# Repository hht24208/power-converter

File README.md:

# STM32 Kontrollü SEPIC Güç Dönüştürücü (Öğrenci Projesi)

Bu repo, güç elektroniği ve kontrol teorisi konseptlerini birleştirerek pratik bir donanıma dönüştürmeyi amaçlayan kişisel bir mühendislik projesidir. Temel hedef, geniş giriş voltajı aralıklarında çalışabilen, yazılım tabanlı (STM32) PID kontrolüne sahip bir SEPIC dönüştürücünün önce LTspice üzerinde matematiksel sınırlarını görmek, ardından gerçek donanımını inşa etmektir.

## 1. Güç Katı ve Donanım Mimarisi
Aşağıdaki şema, SEPIC topolojisinin güç katını ve temel geri besleme (feedback) yapısını göstermektedir. Sistemi mikrodenetleyici ile güvenli bir şekilde sürebilmek için **TC4427** gate sürücü entegresi kullanıldı. Akım ve gerilim okumaları ise **LM358** op-ampları ile STM32'nin ADC pinlerine uygun seviyelere çekildi.

## 2. Matematiksel Modelleme ve Kontrolcü Tasarımı
SEPIC dönüştürücüler 4. dereceden non-lineer sistemler olduğu ve sağ yarı düzlem sıfırı (RHPZ) barındırdığı için, sadece deneme-yanılma ile kontrol edilmeleri oldukça zordur. Bu projede işin teorik kısmına inilerek, sistemin transfer fonksiyonuna uygun bir **Type-II/III Kompansatör** mantığı araştırılmış ve LTspice üzerinde s-domain (Laplace) denklemleriyle modellenmiştir.

## 3. Geçici Hal Yanıtı (Transient Response)
Aşağıdaki simülasyon çıktısında, sisteme aniden 12V giriş (Step Input) uygulandığında donanımın verdiği fiziksel tepki ve PID kontrolcünün davranışı incelenmiştir.
* Simülasyonun ilk milisaniyelerinde, SEPIC topolojisindeki uçan kondansatörün (flying capacitor) dolması sırasında oluşan doğal **Inrush Current (Başlangıç Şoku)** nedeniyle voltaj anlık olarak yükseliyor.
* Kontrolcü bu durumu yakalayarak PWM'i (Duty Cycle) %0'a çekiyor.
* Sistem yaklaşık 11. milisaniyede hedeflediğimiz **5V** seviyesine başarıyla oturarak regülasyonu sağlıyor.

---
*Not: Bu simülasyon aşaması, işin "yazılım-donanım takasını" (hardware vs. software trade-off) analiz etmek için yapılmıştır. İlerleyen aşamalarda KiCad ile PCB tasarımı yapılacak ve gerçek dünyadaki komponent toleransları STM32 üzerindeki C tabanlı bir kontrol algoritmasıyla yönetilmeye çalışılacaktır.*

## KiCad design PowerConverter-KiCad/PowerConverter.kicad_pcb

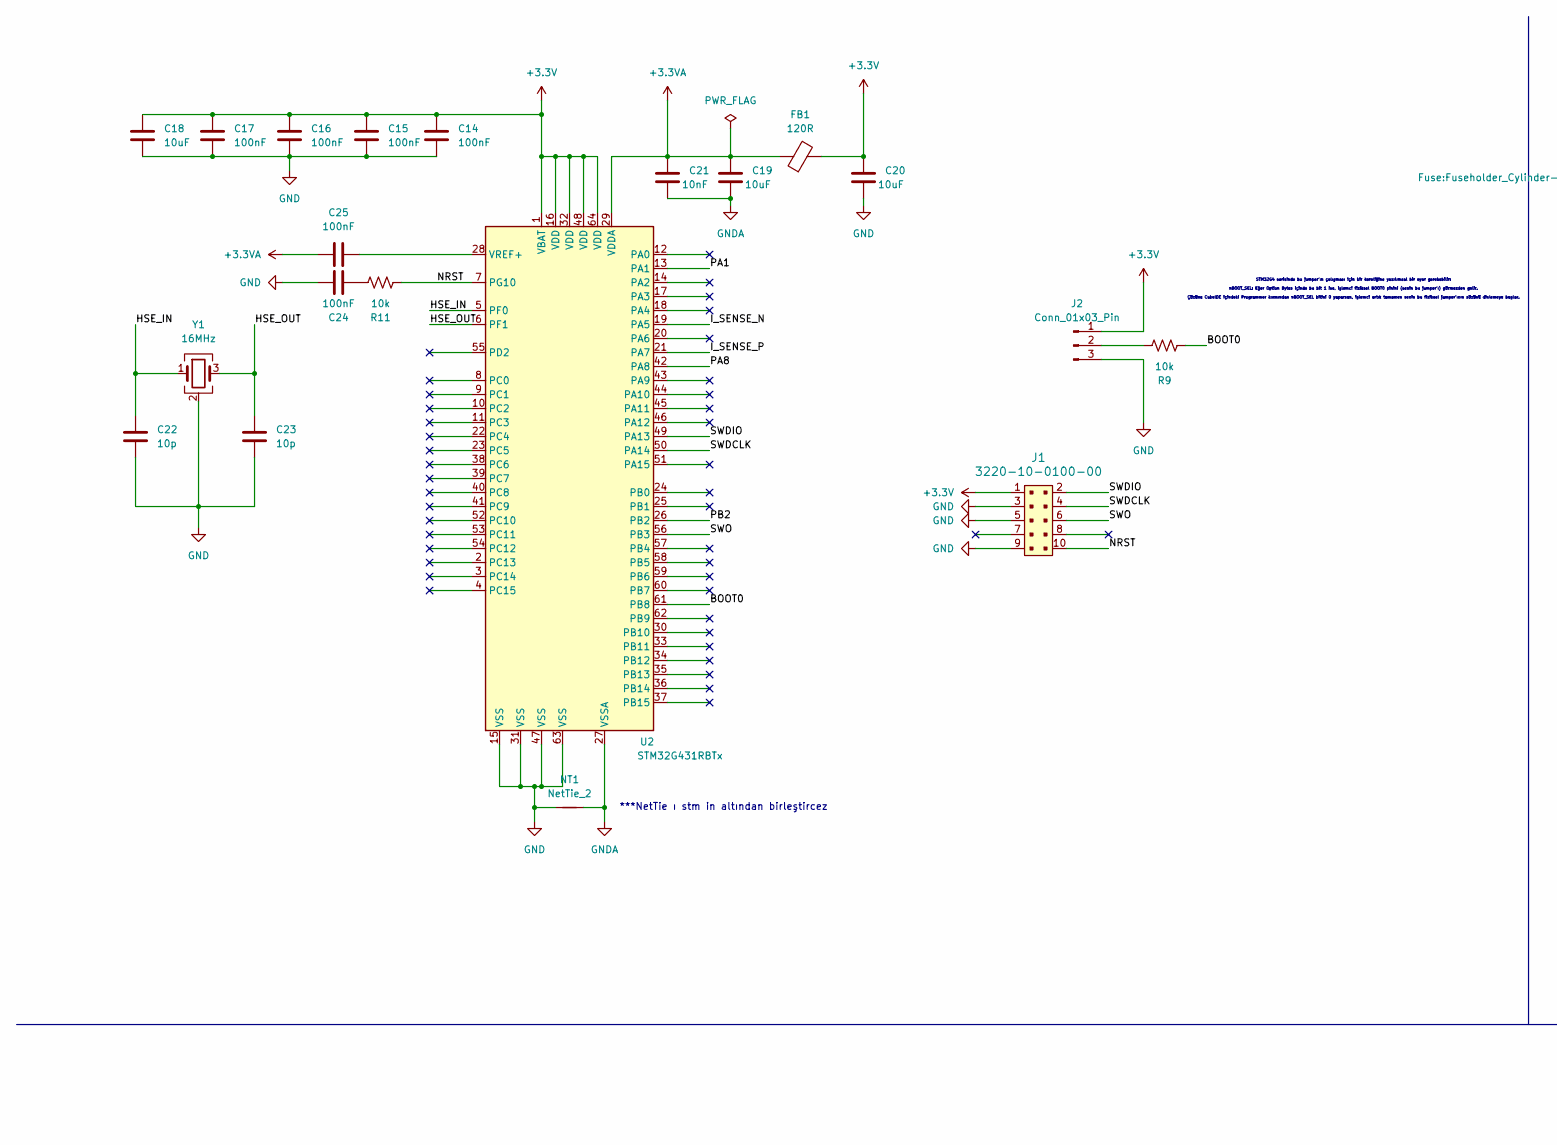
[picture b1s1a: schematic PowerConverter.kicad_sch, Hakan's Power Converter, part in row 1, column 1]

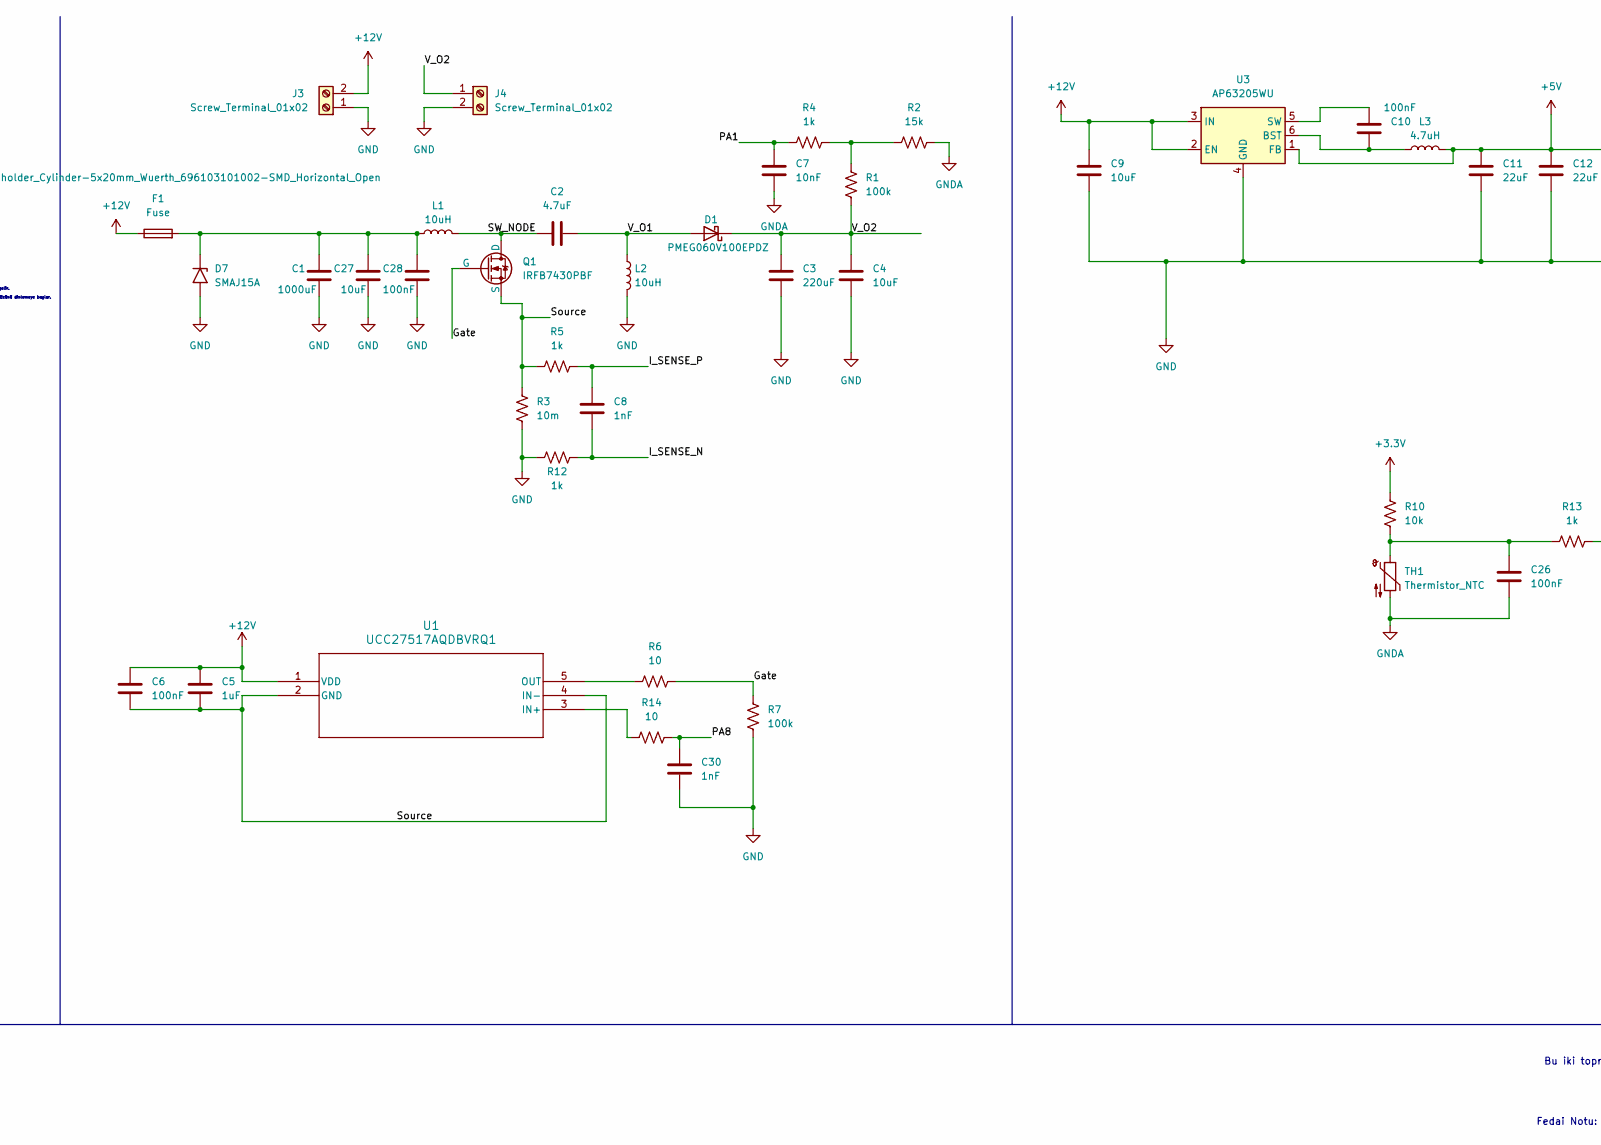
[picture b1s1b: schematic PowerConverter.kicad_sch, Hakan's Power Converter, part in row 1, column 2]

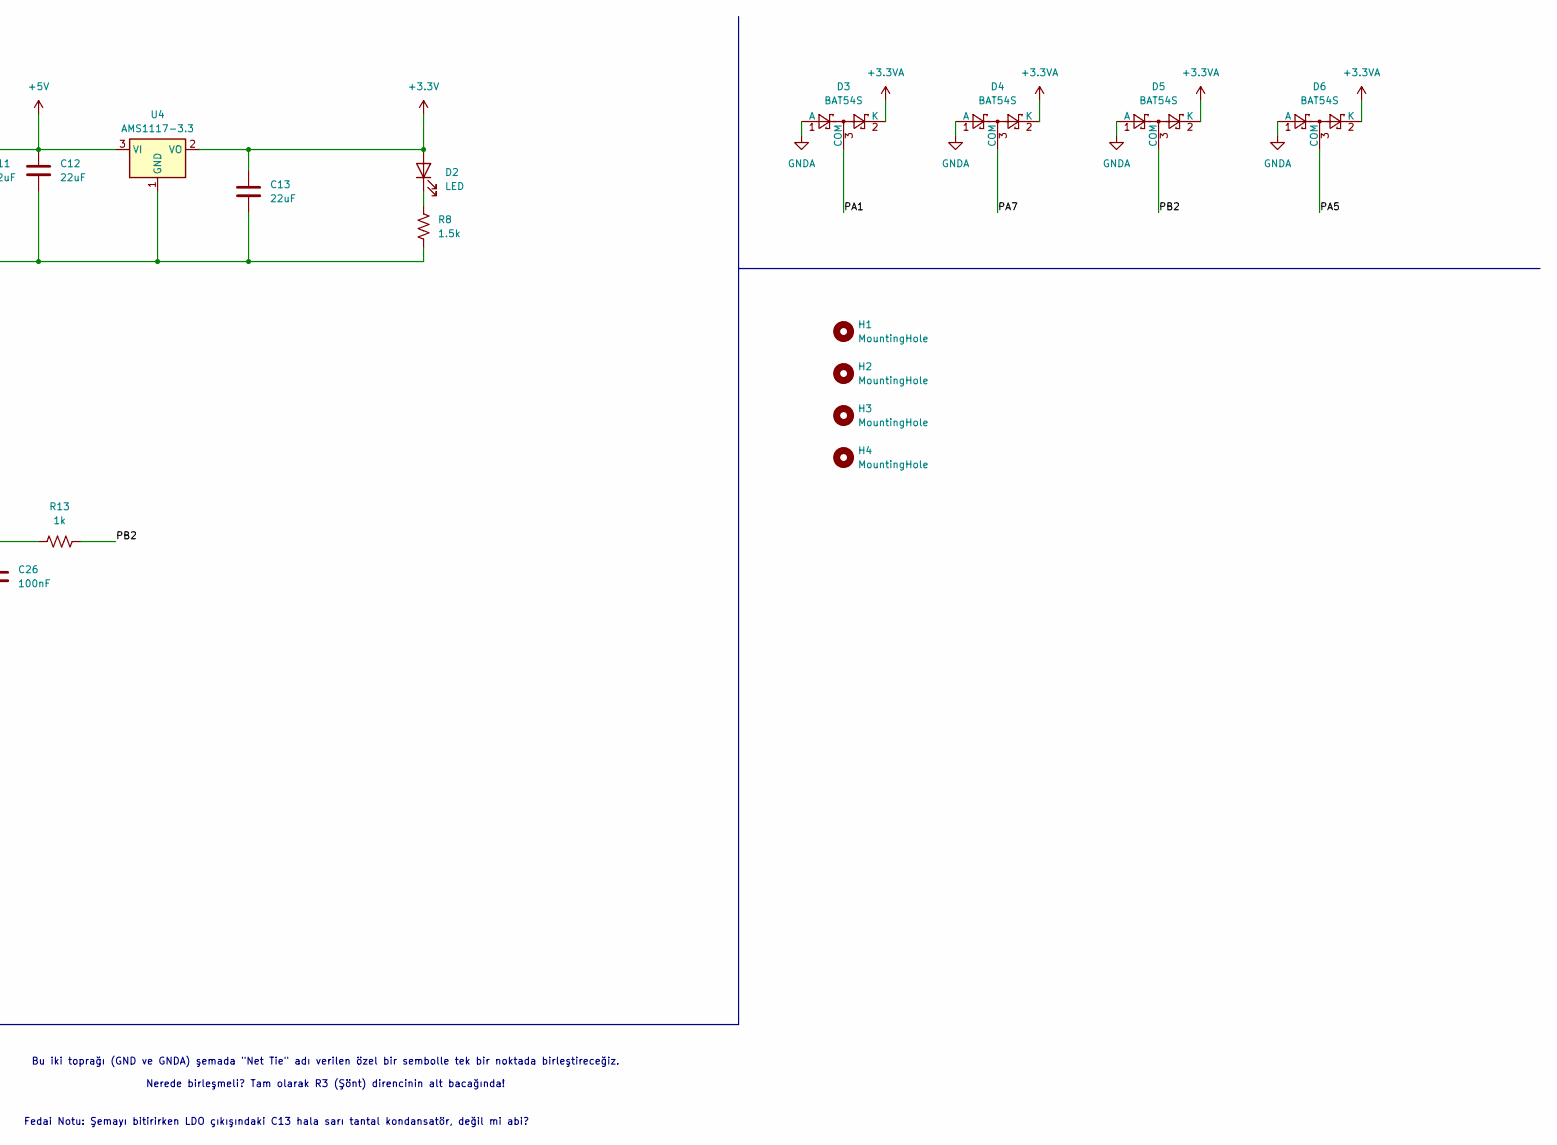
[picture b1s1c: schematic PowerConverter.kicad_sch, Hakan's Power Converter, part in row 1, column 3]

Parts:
C1: 1000uF; CP_Radial_D16.0mm_P7.50mm
C2: 4.7uF; C_1210_3225Metric_Pad1.33x2.70mm_HandSolder
C3: 220uF; CP_Radial_D8.0mm_P5.00mm
C4, C18, C19, C20, C27: 10uF; C_0805_2012Metric_Pad1.18x1.45mm_HandSolder
C5: 1uF; C_0805_2012Metric_Pad1.18x1.45mm_HandSolder
C6, C10, C14, C15, C16, C17, C24, C25, C26, C28: 100nF; C_0603_1608Metric_Pad1.08x0.95mm_HandSolder
C7, C21: 10nF; C_0603_1608Metric_Pad1.08x0.95mm_HandSolder
C8, C30: 1nF; C_0603_1608Metric_Pad1.08x0.95mm_HandSolder
C9: 10uF; C_1210_3225Metric_Pad1.33x2.70mm_HandSolder
C11, C12: 22uF; C_1210_3225Metric_Pad1.33x2.70mm_HandSolder
C13: 22uF; CP_EIA-3528-21_Kemet-B_HandSolder
C22, C23: 10p; C_0603_1608Metric_Pad1.08x0.95mm_HandSolder
D1: PMEG060V100EPDZ; TO-277B
D2: LED; LED_0805_2012Metric_Pad1.15x1.40mm_HandSolder
D3, D4, D5, D6: BAT54S; SOT-23
D7: SMAJ15A; D_SMC
F1: Fuse; Fuseholder_Cylinder-5x20mm_Wuerth_696103101002-SMD_Horizont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
FB1: 120R; L_0603_1608Metric
H1, H2, H3, H4: MountingHole; MountingHole_3.2mm_M3
J1: 3220-10-0100-00; PinHeader_2x5_P1.27mm_Drill.7mm; MPN 3220-10-0100-00; Digi-Key_PN 1175-1627-ND
J2: Conn_01x03_Pin; PinHeader_1x03_P2.54mm_Vertical
J3, J4: Screw_Terminal_01x02; Term_Block_1x2_P5.08MM
L1, L2: 10uH; L_Bourns_SRP1245A
L3: 4.7uH; L_Taiyo-Yuden_NR-30xx
NT1: NetTie_2; NetTie-2_SMD_Pad0.5mm
Q1: IRFB7430PBF; TO-220-3_Vertical
R1, R7: 100k; R_0603_1608Metric_Pad0.98x0.95mm_HandSolder
R2: 15k; R_0603_1608Metric_Pad0.98x0.95mm_HandSolder
R3: 10m; R_2512_6332Metric_Pad1.40x3.35mm_HandSolder
R4, R5, R12, R13: 1k; R_0603_1608Metric_Pad0.98x0.95mm_HandSolder
R6, R14: 10; R_0805_2012Metric_Pad1.20x1.40mm_HandSolder
R8: 1.5k; R_0603_1608Metric_Pad0.98x0.95mm_HandSolder
R9, R10, R11: 10k; R_0603_1608Metric_Pad0.98x0.95mm_HandSolder
TH1: Thermistor_NTC; R_0603_1608Metric_Pad0.98x0.95mm_HandSolder
U1: UCC27517AQDBVRQ1; DBV5_TEX
U2: STM32G431RBTx; LQFP-64_10x10mm_P0.5mm
U3: AP63205WU; TSOT-23-6
U4: AMS1117-3.3; SOT-223-3_TabPin2
Y1: 16MHz; Crystal_SMD_3225-4Pin_3.2x2.5mm

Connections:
+3.3V: C13.1, C14.1, C15.1, C16.1, C17.1, C18.1, C20.1, D2.2 (A), FB1.2, J1.1, J2.1, R10.2, U2.1 (VBAT), U2.16 (VDD), U2.32 (VDD), U2.48 (VDD), U2.64 (VDD), U4.2 (VO)
+3.3VA: C19.1, C21.1, C25.1, D3.2 (K), D4.2 (K), D5.2 (K), D6.2 (K), FB1.1, U2.29 (VDDA)
+5V: C11.1, C12.1, L3.2, U3.1 (FB), U4.3 (VI)
+12V: C5.1, C6.1, C9.1, F1.1, J3.2, U1.1 (VDD), U3.2 (EN), U3.3 (IN)
/BOOT0: R9.2, U2.61 (PB8)
/Gate: Q1.2 (G), R6.2, R7.2
/HSE_IN: C22.1, U2.5 (PF0), Y1.1
/HSE_OUT: C23.1, U2.6 (PF1), Y1.3
/I_SENSE_N: C8.2, R12.2, U2.19 (PA5)
/I_SENSE_P: C8.1, R5.2, U2.21 (PA7)
/NRST: J1.10, R11.2, U2.7 (PG10)
/PA1: C7.1, D3.3 (COM), R4.1, U2.13 (PA1)
/PA5: D6.3 (COM)
/PA7: D4.3 (COM)
/PA8: C30.1, R14.2, U2.42 (PA8)
/PB2: D5.3 (COM), R13.1, U2.26 (PB2)
/SWDCLK: J1.4, U2.50 (PA14)
/SWDIO: J1.2, U2.49 (PA13)
/SWO: J1.6, U2.56 (PB3)
/SW_NODE: C2.1, L1.2, Q1.1 (D)
/Source: C5.2, C6.2, Q1.3 (S), R3.1, R5.1, U1.2 (GND), U1.4 (IN-)
/V_O1: C2.2, D1.2 (A), L2.1
/V_O2: C3.1, C4.1, D1.1 (K), J4.1, R1.2
GND: C1.2, C3.2, C4.2, C9.2, C11.2, C12.2, C13.2, C14.2, C15.2, C16.2, C17.2, C18.2, C20.2, C22.2, C23.2, C24.1, C27.2, C28.2, C30.2, D7.2 (A2), J1.3, J1.5, J1.9, J2.3, J3.1, J4.2, L2.2, NT1.1, R3.2, R7.1, R8.1, R12.1, U2.15 (VSS), U2.31 (VSS), U2.47 (VSS), U2.63 (VSS), U3.4 (GND), U4.1 (GND), Y1.2 (G), Y1.4 (G)
GNDA: C7.2, C19.2, C21.2, C26.2, D3.1 (A), D4.1 (A), D5.1 (A), D6.1 (A), NT1.2, R2.2, TH1.2, U2.27 (VSSA)
unnamed: C24.2, R11.1
unnamed: C26.1, R10.1, R13.2, TH1.1
unnamed: D2.1 (K), R8.2
unnamed: C1.1, C27.1, C28.1, D7.1 (A1), F1.2, L1.1
unnamed: J2.2, R9.1
unnamed: R1.1, R2.1, R4.2
unnamed: R14.1, U1.3 (IN+)
unnamed: R6.1, U1.5 (OUT)
unnamed: C25.2, U2.28 (VREF+)
unnamed: C10.2, L3.1, U3.6 (BST)
unnamed: C10.1, U3.5 (SW)

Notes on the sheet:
***NetTie ı stm in altından birleştircez
Bu iki toprağı (GND ve GNDA) şemada "Net Tie" adı verilen özel bir sembolle tek bir noktada birleştireceğiz. Nerede birleşmeli? Tam olarak R3 (Şönt) direncinin alt bacağında!
STM32G4 serisinde bu jumper'ın çalışması için bir kereliğine yazılımsal bir ayar gerekebilir: nBOOT_SEL: Eğer Option Bytes içinde bu bit 1 ise, işlemci fiziksel BOOT0 pinini (senin bu jumper'ı) görmezden gelir. Çözüm: CubeIDE içindeki Programmer kısmından nBOOT_SEL bitini 0 yaparsan, işlemci artık 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
Fedai Notu: Şemayı bitirirken LDO çıkışındaki C13 hala sarı tantal kondansatör, değil mi abi?

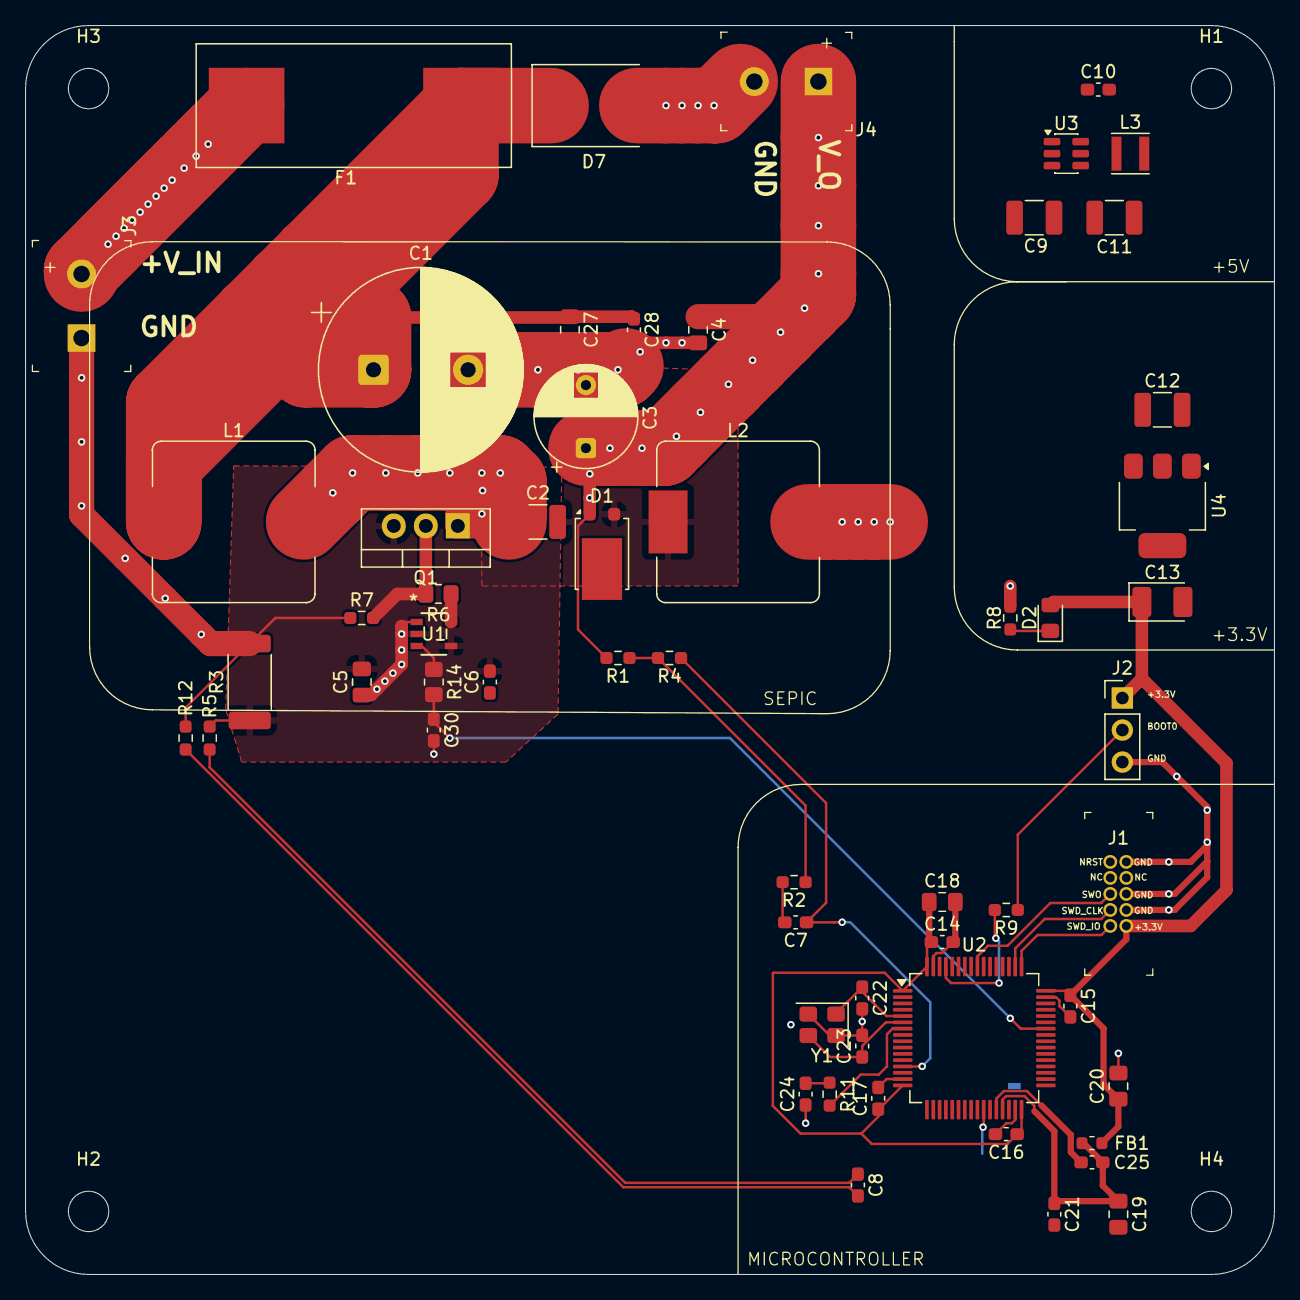
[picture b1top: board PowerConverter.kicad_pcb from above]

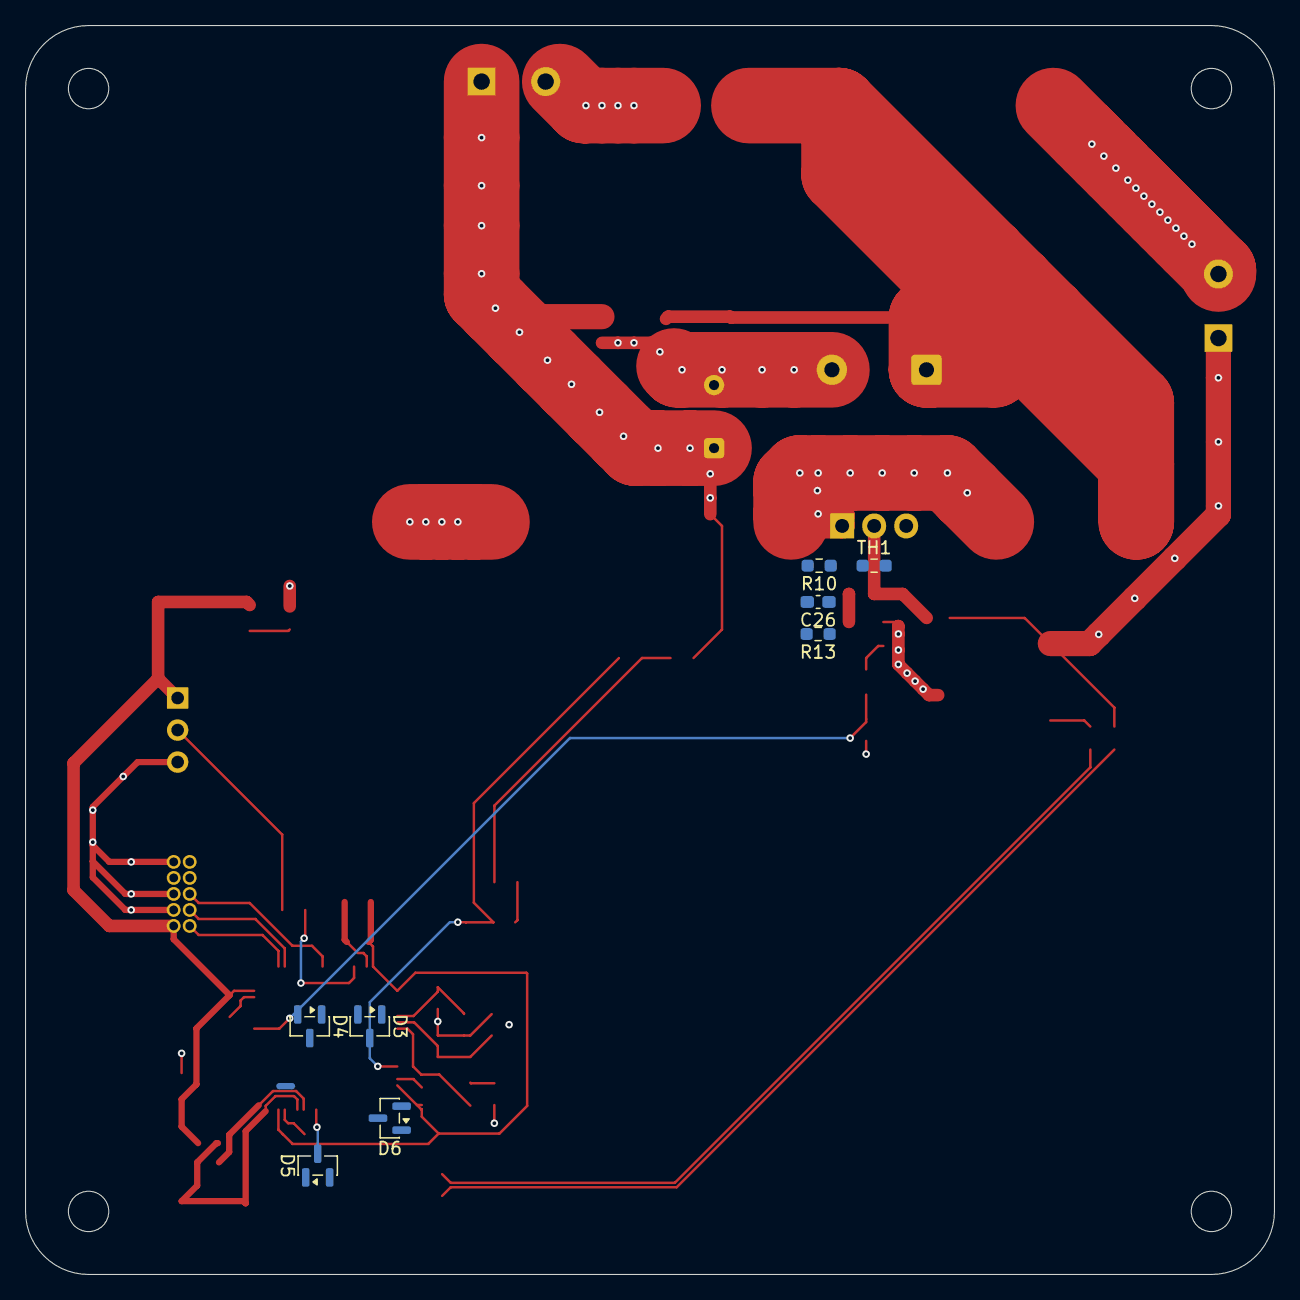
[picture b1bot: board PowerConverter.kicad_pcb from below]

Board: 4 copper layers, 99.1 x 99.1 mm, 71 parts (9 on the bottom side), 34 nets.

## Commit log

2026-03-08 feat: initial SEPIC design with TC4427 driver and MC34063A aux boost
2026-03-08 hardware: finalized SEPIC power stage, added bulletproof LM358/TC4427 spice models, and implemented active low-pass filtered current/voltage sensing
2026-03-08 feat: SEPIC analog simulation complete with full PID tuning, TC4427 driver, and LM358 current sensing
2026-03-09 feat: SEPIC güç dönüştürücü LTspice simülasyonları, komponent modelleri (LM358, TC4427, IRFB7430) ve PWM jeneratör eklendi
2026-03-09 docs: README guncellendi, LTspice devre mimarisi, PID modeli ve osiloskop sonuclari eklendi
2026-03-09 feat: KiCad PowerConverter projesi baslatildi. TODO: Yarin ilk is Schottky diyot semaya eklenecek.
2026-03-11 feat: gate driver eklendi, feedback pinleri (PA1, PA7) ayarlandı. Sırada 12V-3.3V STM beslemesi var.
2026-03-11 security: token.txt dosyası gitignore listesine eklendi
2026-03-12 refactor(hardware): Optimize grounding architecture and power stability
    - Fixed AMS1117-3.3 feedback loop to prevent 6.6V overvoltage.
    - Implemented 4-wire Kelvin connection (Net-Tie) for precise 10mOhm current sensing.
    - Added 10-ohm gate resistor to UCC27517 to prevent MOSFET gate ringing.
    - Safely routed UCC27517 IN- pin to GND.
    - Isolated HSE (16MHz) crystal ground strictly to digital GND to protect analog signal integrity.
    - Ensured C13 is a Tantalum capacitor for LDO stability (Mental note preserved).
2026-03-12 refactor: STM32G431 işlemci pin eşleşmeleri ve sinyal bütünlüğü iyileştirmeleri
    Bu güncelleme ile donanım mimarisi endüstriyel standartlara getirilmiştir:
    - Kristal (HSE) pinleri, G431 mimarisine uygun olarak PF0/PF1 bacaklarına taşındı.
    - NRST hattı PG10 (Pin 7) üzerine 100nF filtre ile tanımlandı; sistem kararlılığı artırıldı.
    - BOOT0 (PB8) pini 10k pull-down direnci ile mühürlenerek kararsız çalışma modları engellendi.
    - ADC hassasiyeti için VREF+ ve VDDA filtreleme katları revize edildi.
    - Güç katı (5A SEPIC) toprak dönüşleri, analog bölgeden (GNDA) izole edilerek sistem gürültüsü minimize edildi.
2026-03-13 feat: SEPIC çevirici Simulink modeli gerçekçi parametrelerle optimize edildi
    - Anahtarlama frekansı 300kHz'e çıkarıldı.
    - Bourns SRP1265A-100M (10uH, 16.5mOhm) bobin modeli entegre edildi.
    - MBR1045 Schottky diyot modeli (Vf ve Ron değerleriyle) eklendi.
    - Yakınsama hatalarını çözmek için 100k sızıntı dirençleri eklendi.
    - ode23t çözücüsüne geçildi ve yerel Backward Euler aktif edildi.
    - Kapasitörlere 30mOhm ESR eklenerek nümerik stabilite sağlandı.
2026-03-14 MATLAB analizleri Zero Crossing hataları nedeniyle askıya alındı (14.03.2026). Simülasyon nazıyla uğraşmak yerine fiziksel sistem için KiCad PCB Layout sürecine geçildi.
2026-03-14 Şema ve BOM optimizasyonu tamamlandı. PCB Layout aşamasına geçiliyor.
2026-03-15 Layout: Buck ve LDO yerleşimi tamamlandı, sakin ada stratejisi uygulandı
2026-03-21 SEPIC v2.0: 4-Layer Stackup, 12V Power Plane on In2, and High Current Via Stitching implemented
2026-03-21 Layout update: PA8 bottom layer shielding, U1 RC filter optimization, VDDA daisy-chain routing, and via-in-pad corrections
